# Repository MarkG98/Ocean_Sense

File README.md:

# Ocean_Sense

Ocean Sense is an ocean-sensing platform which can be placed on a buoy or other ocean science apparatus and sent out to sea for about one week at a time. Many ocean science experiments are run off of buoys or other devices that stand alone in the field for an extended period of time. This board serves as a packaged sensor set that measures and logs three local conditions during the experiments: **temperature, humidity**, and **acceleration**. The board sits ontop of a buoy or equivalent flotation device for the duration of an experiment and then is retrieved. To travel into the depths of the ocean, an appropriate case will need to be engineered.

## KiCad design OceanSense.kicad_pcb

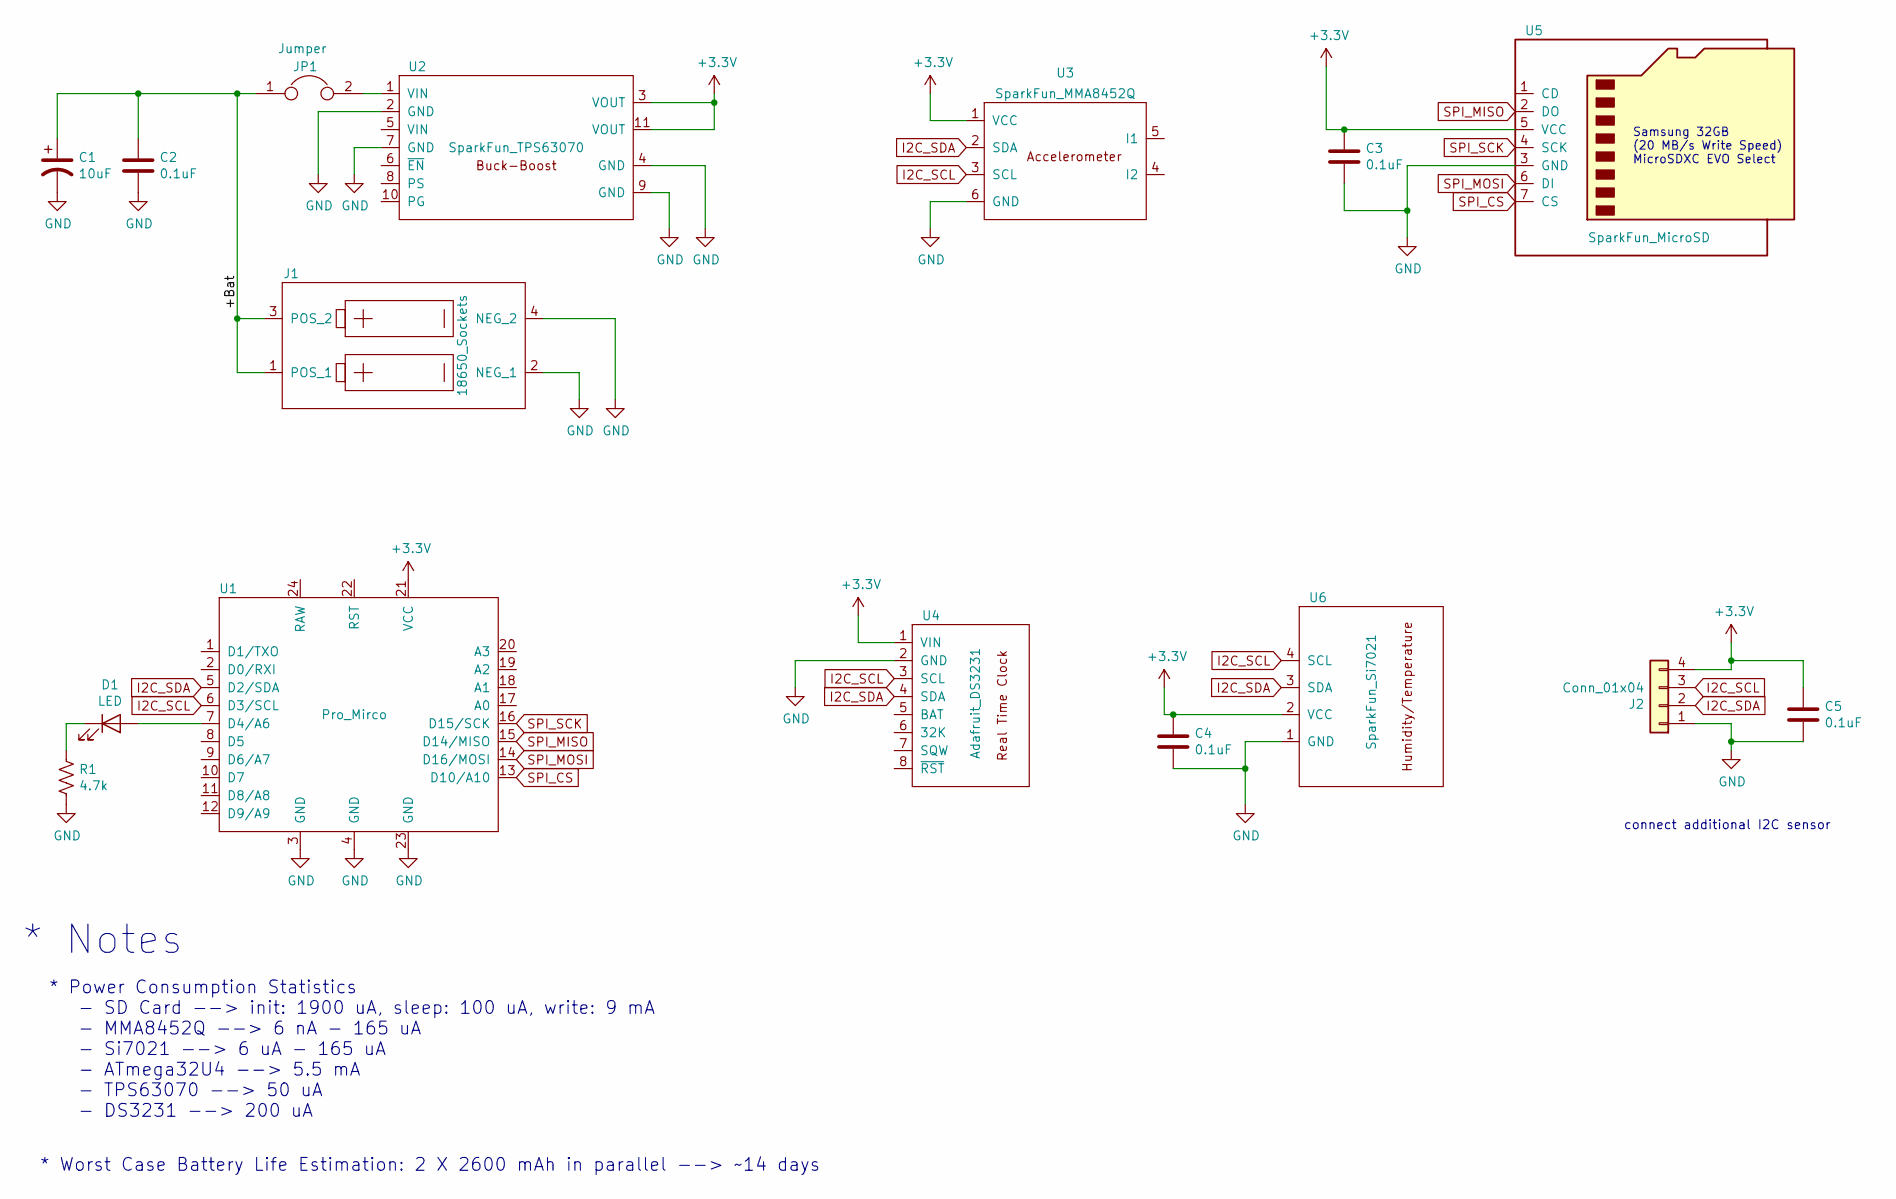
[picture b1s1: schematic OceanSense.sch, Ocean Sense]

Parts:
C1: 10uF; CP_Radial_D5.0mm_P2.50mm
C2, C3, C4, C5: 0.1uF; C_Rect_L4.0mm_W2.5mm_P2.50mm
D1: LED; LED_D3.0mm
J1: 18650_Sockets; 36-1049-ND
J2: Conn_01x04; Molex_KK-254_AE-6410-04A_1x04_P2.54mm_Vertical
JP1: Jumper
R1: 4.7k; Resistor
U1: Pro_Mirco; Pro Micro
U2: SparkFun_TPS63070; TPS63070
U3: SparkFun_MMA8452Q; MMA8452Q
U4: Adafruit_DS3231; DS3231
U5: SparkFun_MicroSD; uSD Breakout
U6: SparkFun_Si7021; Si7021

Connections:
+3V3: C3.1, C4.1, C5.1, J2.4, U1.21 (VCC), U2.3 (VOUT), U2.11 (VOUT), U3.1 (VCC), U4.1 (VIN), U5.5 (VCC), U6.2 (VCC)
/+Bat: C1.1, C2.1, J1.1 (POS_1), J1.3 (POS_2), JP1.1
GND: C1.2, C2.2, C3.2, C4.2, C5.2, J1.2 (NEG_1), J1.4 (NEG_2), J2.1, R1.2, U1.3 (GND), U1.4 (GND), U1.23 (GND), U2.2 (GND), U2.4 (GND), U2.7 (GND), U2.9 (GND), U3.6 (GND), U4.2 (GND), U5.3 (GND), U6.1 (GND)
I2C_SCL: J2.3, U1.6 (D3/SCL), U3.3 (SCL), U4.3 (SCL), U6.4 (SCL)
I2C_SDA: J2.2, U1.5 (D2/SDA), U3.2 (SDA), U4.4 (SDA), U6.3 (SDA)
unnamed: D1.1 (K), R1.1
unnamed: D1.2 (A), U1.7 (D4/A6)
unnamed: JP1.2, U2.1 (VIN)
SPI_CS: U1.13 (D10/A10), U5.7 (CS)
SPI_MISO: U1.15 (D14/MISO), U5.2 (DO)
SPI_MOSI: U1.14 (D16/MOSI), U5.6 (DI)
SPI_SCK: U1.16 (D15/SCK), U5.4 (SCK)

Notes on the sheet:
* Power Consumption Statistics - SD Card --> init: 1900 uA, sleep: 100 uA, write: 9 mA - MMA8452Q --> 6 nA - 165 uA - Si7021 --> 6 uA - 165 uA - ATmega32U4 --> 5.5 mA - TPS63070 --> 50 uA - DS3231 --> 200 uA
Samsung 32GB (20 MB/s Write Speed) MicroSDXC EVO Select
* Worst Case Battery Life Estimation: 2 X 2600 mAh in parallel --> ~~14 days
* Notes
connect additional I2C sensor

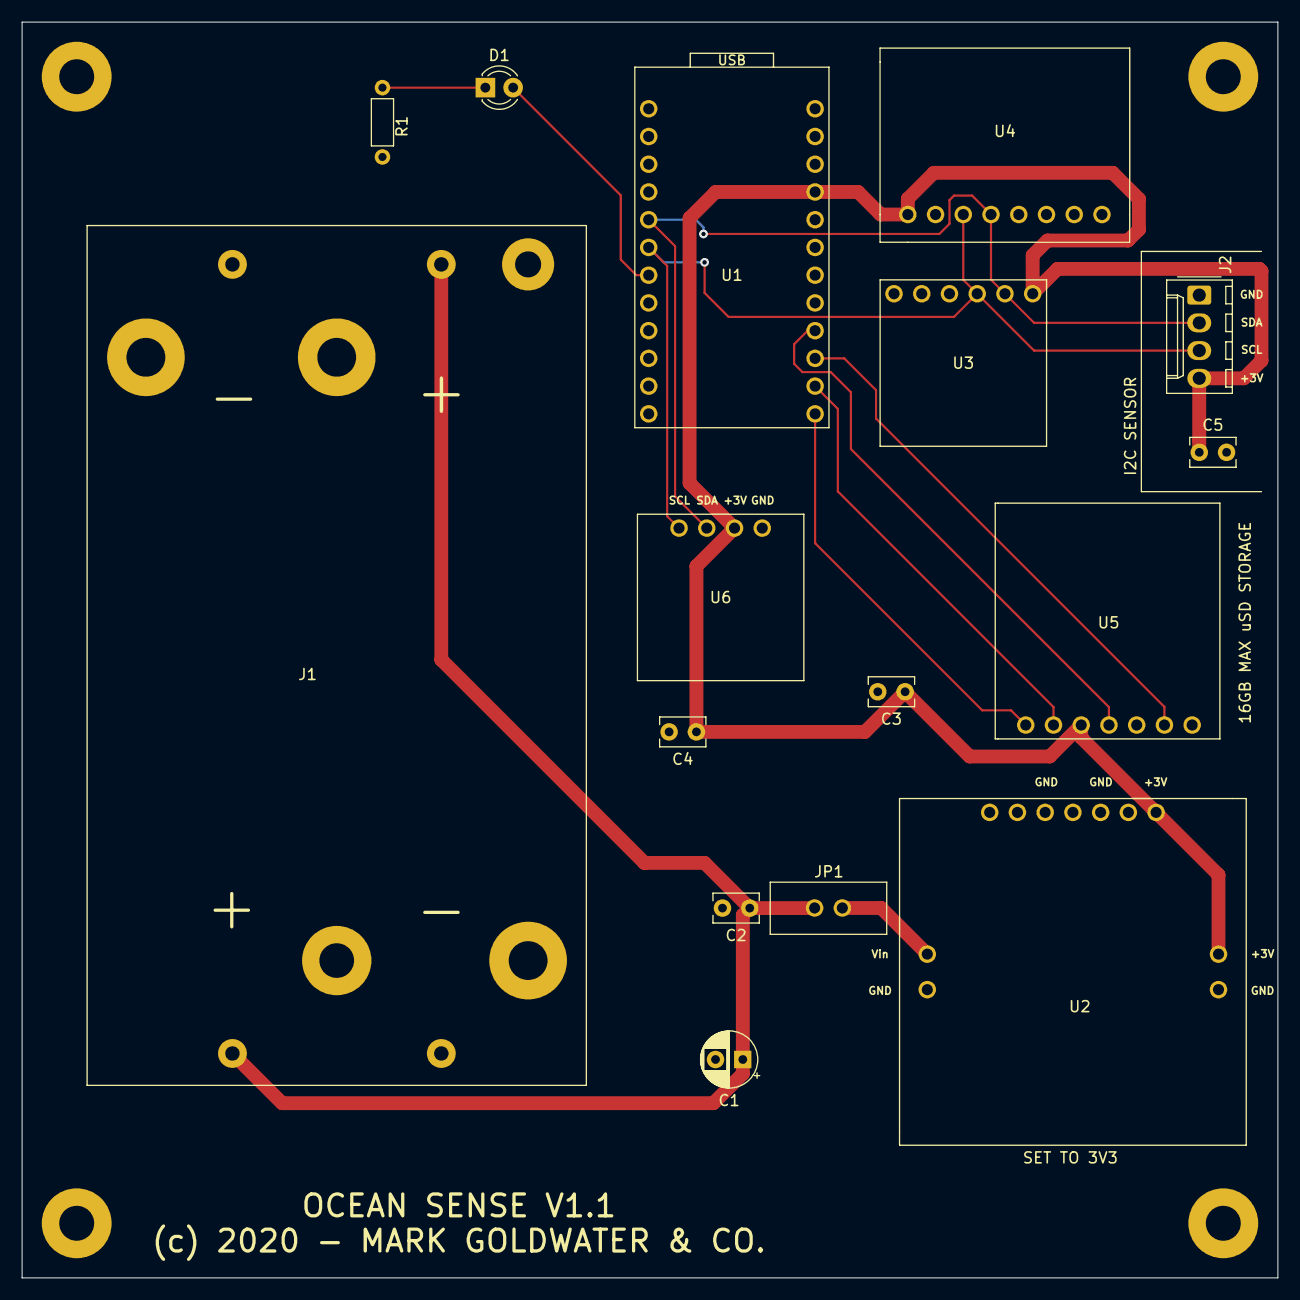
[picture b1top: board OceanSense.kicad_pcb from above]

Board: 2 copper layers, 115.0 x 115.0 mm, 16 parts (0 on the bottom side), 12 nets.

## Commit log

2020-12-01 Push current project
2020-12-02 Modified file writing to be in CSV format
2020-12-04 Adding board image
2020-12-04 Changed capitalization on folder
2020-12-04 Added board image
2020-12-04 Resized image
2020-12-17 Adding summary to README.md
2020-12-17 Adding images
2020-12-17 Fixing board image

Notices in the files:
OceanSense.kicad_pcb:
(c) 2020 - MARK GOLDWATER & CO.
